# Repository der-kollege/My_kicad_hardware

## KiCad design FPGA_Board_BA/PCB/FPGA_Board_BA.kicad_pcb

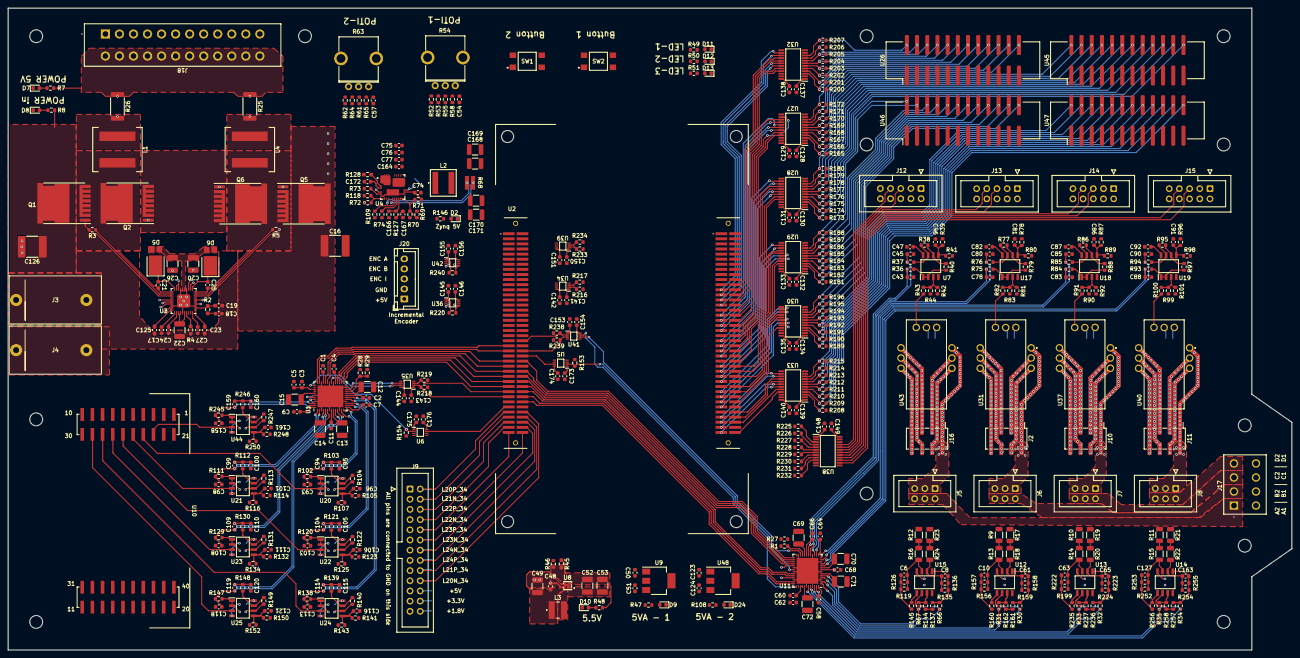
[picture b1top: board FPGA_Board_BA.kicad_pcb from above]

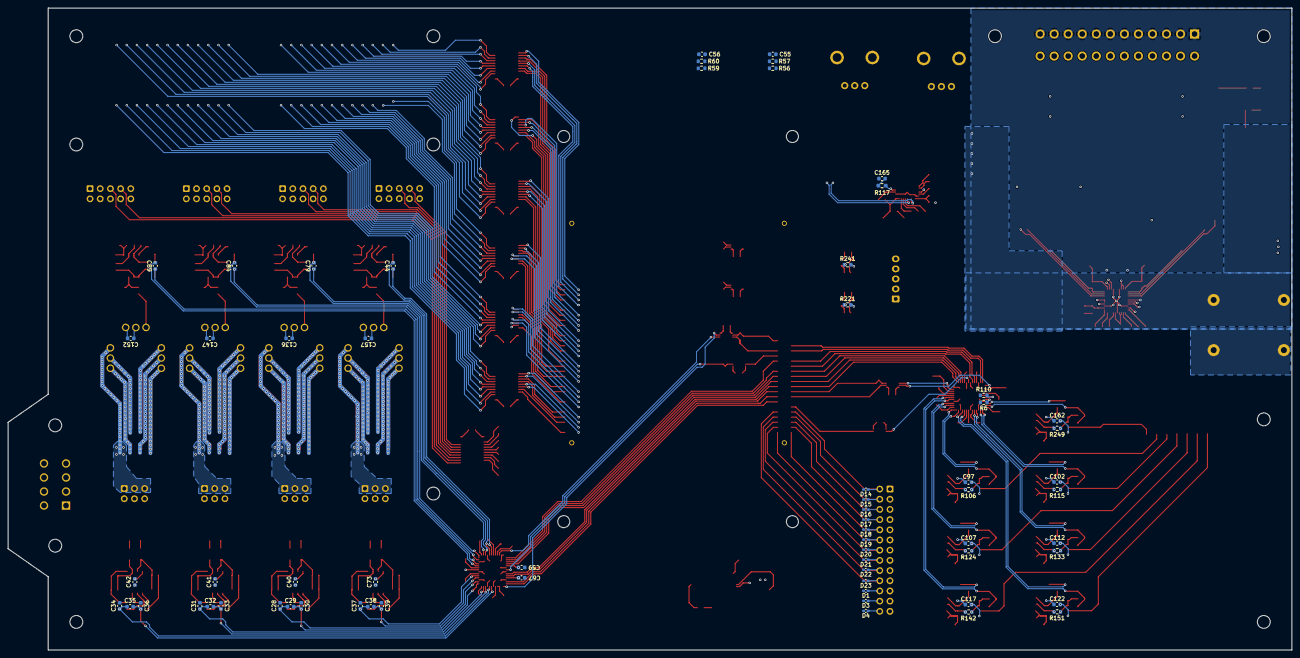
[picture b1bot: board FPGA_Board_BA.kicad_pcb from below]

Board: 4 copper layers, 320.0 x 160.0 mm, 524 parts (65 on the bottom side), 390 nets.

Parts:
C1, C2, C11, C24, C50, C51, C58, C59, C68, C123, C124: 1u_0603; C_0603
C3, C4, C5, C6, C7, C8, C9, C10, C40, C41, C42, C46, C47, C48, C54, C55, C56, C57, C60, C61, C62, C63, C64, C65, C66, C67, C73, C81, C82, C86, C87, C91, C92, C96, C97, C101, C102, C106, C107, C111, C112, C116, C117, C121, C122, C127, C128, C129, C130, C131, C132, C133, C134, C135, C136, C137, C138, C139, C140, C141, C142, C143, C144, C145, C146, C147, C148, C149, C150, C151, C152, C153, C154, C155, C156, C157, C161, C162, C163, C173, C174, C175, C176: 100n_0603; C_0603
C12, C13, C14, C15, C20, C22, C26, C49, C52, C53, C69, C70, C71, C72: 10u_1210; C_1210
C16, C126: 25uF_2220; C_2220_5650Metric_Pad1.97x5.40mm_HandSolder
C17, C21, C25, C27, C75, C76, C77, C164, C165: 4u7_0603; C_0603
C18: 1n_0603; C_0603
C19: 56pF_0603; C_0603_1608Metric_Pad1.08x0.95mm_HandSolder
C23, C125: 120nF_0603; C_0603_1608Metric_Pad1.08x0.95mm_HandSolder
C28, C29, C30, C31, C32, C33, C34, C35, C36, C37, C38, C39, C43, C44, C45, C78, C79, C80, C83, C84, C85, C88, C89, C90, C93, C94, C95, C98, C99, C100, C103, C104, C105, C108, C109, C110, C113, C114, C115, C118, C119, C120, C158, C159, C160: 15p_0603; C_0603
C74: 470n_0603; C_0603
C166: 220p_0603; R_0603_1608Metric
C167, C172: 15n_0603; C_0603
C168, C169, C170, C171: 47u_1210; C_1210_3225Metric
D1, D3, D4, D14, D15, D16, D17, D18, D19, D20, D21, D22, D23: B72590D50H160; C_0402_1005Metric_Pad0.74x0.62mm_HandSolder
D2, D7, D8, D9, D10, D12, D24: LED_G_0603; LED_0603_1608Metric
D5, D6: SBR10U200P5-13; SBR10U200P5
D11: LED_B_0603; LED_0603_1608Metric
D13: LED_R_0603; LED_0603_1608Metric
J2, J10, J11, J16: PinHeader_2x4_SMD; PinHeader_2x04_P2.54mm_Vertical_SMD
J3: Banana_Socket_Red; Banana_Socket_Altech_Red
J4: Banana_Socket_Black; Banana_Socket_Aletch_Black
J5, J6, J7, J8: Box_Header_6pin; IDC-Header_2x03_P2.54mm_Vertical
J9: Box_Header_26pin; IDC-Header_2x13_P2.54mm_Vertical
J12, J13, J14, J15: Box_Header_2x05_THT; IDC-Header_2x05_P2.54mm_Vertical
J17: Plug_Terminal_2x4_Vertical
J18: Plug_Terminal_2x12pin; DMCV 1,5_12-G1F-3,5-LR P20THR
J20: JST_XH_05_vertical; JST_XH_B5B-XH-A_1x05_P2.50mm_Vertical
L1, L4: XAL1010-152MED; L_Coilcraft_XAL1010-XXX
L2: Inductor 5.6uH; L_5u6_78439346056
L3: SMD_Inductor_1u; 74404043010A
Q1, Q2, Q5, Q6: IPT017N12NM6; Infineon_PG-HSOF-8-1
R1, R27, R28, R29, R72, R118, R220, R221, R240, R241: 0R_0603; R_0603_1608Metric
R2: 25k5_0603; R_0603_1608Metric_Pad0.98x0.95mm_HandSolder
R3, R5: 2R2_0603; R_0603_1608Metric
R4: 39k2_0603; R_0603_1608Metric_Pad0.98x0.95mm_HandSolder
R6, R43, R82, R91, R100, R110, R119, R126, R135, R136, R137, R144, R145, R156, R157, R158, R159, R160, R161, R162, R199, R222, R223, R224, R235, R236, R237, R252, R253, R254, R255, R256, R257, R258: 1k_0603; R_0603_1608Metric
R7, R47, R48, R49, R50, R51, R52, R53, R55, R57, R60, R61, R62, R64, R70, R108, R146, R153, R154, R165, R166, R167, R168, R169, R170, R171, R172, R173, R174, R175, R176, R177, R178, R179, R180, R181, R182, R183, R184, R185, R186, R187, R188, R189, R190, R191, R192, R193, R194, R195, R196, R200, R201, R202, R203, R204, R205, R206, R207, R208, R209, R210, R211, R212, R213, R214, R215, R216, R217, R218, R219, R225, R226, R227, R228, R229, R230, R231, R232, R233, R234, R238, R239: 10k_0603; R_0603_1608Metric
R8, R46, R73: 100k_0603; R_0603_1608Metric
R9, R10, R11, R12, R13, R14, R15, R16, R17, R18, R19, R20, R21, R22, R23, R24: 100k_1206; R_1206_3216Metric
R25, R26: 0R002_2512; R_2512_6332Metric
R30, R31, R32, R33, R34, R35, R36, R37, R66, R67, R75, R76, R84, R85, R93, R94, R102, R103, R111, R112, R120, R121, R129, R130, R138, R139, R147, R148, R245, R246: 30R_0603; R_0603_1608Metric
R38, R40, R77, R79, R86, R88, R95, R97, R104, R106, R113, R115, R122, R124, R131, R133, R140, R142, R149, R151, R247, R249: 500R_0603; R_0603_1608Metric
R39, R41, R78, R80, R87, R89, R96, R98, R105, R107, R114, R116, R123, R125, R132, R134, R141, R143, R150, R152, R248, R250: 5k1_0603; R_0603_1608Metric
R42, R44, R81, R83, R90, R92, R99, R101: 9k1_0603; R_0603_1608Metric
R45: 820k_0603; R_0603_1608Metric_Pad0.98x0.95mm_HandSolder
R54, R63: Poti_10k; RK09D1130A1N
R56, R58, R59, R65: 100R_0603; R_0603_1608Metric
R68: Shunt_0R006; PRL1632-R006-F-T1
R69: 52K3_0603; R_0603_1608Metric
R71: 24k9_0603; R_0603_1608Metric
R74: 71k5_0603; R_0603_1608Metric
R109: 41k2_0603; R_0603_1608Metric
R117, R128: 1R_0603; R_0603_1608Metric_Pad0.98x0.95mm_HandSolder
R127: 3k83_0603; R_0603_1608Metric
SW1, SW2: TL3305BF100QG; TL3305BF160QG
U1, U11: LTC2320-16_CMOS; UKG_52_7mm_8mm
U2: Zynq7020
U3: LM5143; VQFN 40 pin 5.8mm x 5.8mm
U4: LM70860RRXR; RRX Package, 29-Pin VQFN
U5, U6, U34, U35, U36, U39, U41, U42: SN74LXC2T45Q1; SN74LXC2T45QDCURQ1
U7, U12, U13, U14, U15, U17, U18, U19, U20, U21, U22, U23, U24, U25, U44: 1819_IS8; LT1819
U8: TPS61022
U9, U48: MCP1703AT-5002EDB; SOT-223
U10: BOOSTXL-3PHGANINV; TI_BOOSTXL_3PH
U26, U45, U46, U47: BoxHeader_24pin; IDC-Header_2x12_P2.54mm_Vertical_SMD
U27, U28, U29, U30, U32, U33, U38: SN74LXCH8T245RHLR; SN74LXCH8T245
U31, U37, U40, U43: S22P006S05; Tamura_S22P006S05

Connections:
+1V8: C1.1, C4.1, C59.1, C67.1, C144.1, C154.1, C173.2, C175.2, D4.1 (A1), J9.26, R1.2, R28.2, U1.31 (OVDD), U1.37 (OVDD), U2.b9 (XADC_VCC), U5.1 (VCCA), U6.1 (VCCA), U11.31 (OVDD), U11.37 (OVDD), U35.8 (VCCB), U41.8 (VCCB)
+3.3V: C129.1, C131.1, C133.1, C135.1, C138.1, C140.1, C142.1, C143.2, C146.1, C148.2, C151.1, C153.2, C156.1, C174.1, C176.1, D3.1 (A1), J9.24, R218.1, R219.1, R225.1, R226.1, R227.1, R228.1, R229.1, R230.1, R231.1, R232.1, R238.1, R239.1, SW1.3, SW1.4, SW2.3, SW2.4, U2.a3 (VDD_3V), U2.b3 (VDD_3V), U5.8 (VCCB), U6.8 (VCCB), U27.23 (V_{CCB}), U27.24 (V_{CCB}), U28.23 (V_{CCB}), U28.24 (V_{CCB}), U29.23 (V_{CCB}), U29.24 (V_{CCB}), U30.23 (V_{CCB}), U30.24 (V_{CCB}), U32.23 (V_{CCB}), U32.24 (V_{CCB}), U33.23 (V_{CCB}), U33.24 (V_{CCB}), U34.8 (VCCB), U35.1 (VCCA), U36.8 (VCCB), U38.1 (V_{CCA}), U38.2 (DIR), U39.8 (VCCB), U41.1 (VCCA), U42.8 (VCCB)
+5V: C48.1, C49.1, C128.2, C130.2, C132.2, C134.2, C137.2, C139.2, C141.2, C145.2, C149.1, C150.2, C155.2, D1.1 (A1), J9.22, J12.9, J12.10, J13.9, J13.10, J14.9, J14.10, J15.9, J15.10, J18.2, J18.4, J18.6, J18.8, J18.10, J18.12, J18.14, J18.16, J18.18, J18.20, J18.22, J18.24, J20.1, L3.1, R7.1, R25.1, R26.1, R165.1, R166.1, R167.1, R168.1, R169.1, R170.1, R171.1, R172.1, R173.1, R174.1, R175.1, R176.1, R177.1, R178.1, R179.1, R180.1, R181.1, R182.1, R183.1, R184.1, R185.1, R186.1, R187.1, R188.1, R189.1, R190.1, R191.1, R192.1, R193.1, R194.1, R195.1, R196.1, R200.1, R201.1, R202.1, R203.1, R204.1, R205.1, R206.1, R207.1, R208.1, R209.1, R210.1, R211.1, R212.1, R213.1, R214.1, R215.1, R216.1, R217.1, R220.1, R233.1, R234.1, R240.1, U3.5 (VOUT2), U3.6 (VCCX), U3.26 (VOUT1), U8.5 (EN), U8.7 (VIN), U27.1 (V_{CCA}), U27.2 (DIR), U28.1 (V_{CCA}), U28.2 (DIR), U29.1 (V_{CCA}), U29.2 (DIR), U30.1 (V_{CCA}), U30.2 (DIR), U32.1 (V_{CCA}), U32.2 (DIR), U33.1 (V_{CCA}), U33.2 (DIR), U34.1 (VCCA), U36.1 (VCCA), U38.23 (V_{CCB}), U38.24 (V_{CCB}), U39.1 (VCCA), U42.1 (VCCA)
+5VA: C2.1, C3.1, C5.1, C7.1, C9.1, C40.2, C41.2, C42.2, C47.1, C51.1, C58.1, C60.1, C62.1, C64.1, C66.1, C73.2, C82.1, C87.1, C92.1, C97.1, C102.1, C107.1, C112.1, C117.1, C122.1, C162.1, R47.1, R52.1, R53.1, R55.1, R61.1, R62.1, R64.1, U1.15 (VDD), U1.21 (VDD), U1.43 (REFBUFEN), U1.44 (VDD), U1.52 (VDD), U7.8 (V+), U9.3 (Vout), U11.15 (VDD), U11.21 (VDD), U11.43 (REFBUFEN), U11.44 (VDD), U11.52 (VDD), U12.4 (V-), U13.4 (V-), U14.4 (V-), U15.4 (V-), U17.8 (V+), U18.8 (V+), U19.8 (V+), U20.8 (V+), U21.8 (V+), U22.8 (V+), U23.8 (V+), U24.8 (V+), U25.8 (V+), U44.8 (V+)
+5VA_2: C124.1, C136.2, C147.2, C152.2, C157.2, R108.1, U31.9 (5V), U37.9 (5V), U40.9 (5V), U43.9 (5V), U48.3 (Vout)
+5V_Zynq: C168.2, C169.2, C170.2, C171.2, R68.2, R69.1, R146.1, U2.a1 (VDD_5V), U2.b1 (VDD_5V), U4.6 (BIAS), U4.12 (Vout)
/ADC for B6/CLK_IN: R218.2, U2.a65 (IO_L16N_T2_34), U35.2 (A1)
/ADC for B6/CLK_OUT: U2.a69 (IO_L18N_T2_34), U6.7 (B1)
/ADC for B6/Diffamp_1/Ain+: C158.1, C159.1, R245.1, U1.51 (Ain7+)
/ADC for B6/Diffamp_1/Ain-: C159.2, C160.1, R246.1, U1.50 (Ain7-)
/ADC for B6/Diffamp_2/Ain+: C93.1, C94.1, R102.1, U1.14 (Ain3+)
/ADC for B6/Diffamp_2/Ain-: C94.2, C95.1, R103.1, U1.13 (Ain3-)
/ADC for B6/Diffamp_3/Ain+: C98.1, C99.1, R111.1, U1.2 (Ain6+)
/ADC for B6/Diffamp_3/Ain-: C99.2, C100.1, R112.1, U1.1 (Ain6-)
/ADC for B6/Diffamp_4/Ain+: C103.1, C104.1, R120.1, U1.17 (Ain2+)
/ADC for B6/Diffamp_4/Ain-: C104.2, C105.1, R121.1, U1.16 (Ain2-)
/ADC for B6/Diffamp_5/Ain+: C108.1, C109.1, R129.1, U1.5 (Ain5+)
/ADC for B6/Diffamp_5/Ain-: C109.2, C110.1, R130.1, U1.4 (Ain5-)
/ADC for B6/Diffamp_6/Ain+: C113.1, C114.1, R138.1, U1.20 (Ain1+)
/ADC for B6/Diffamp_6/Ain-: C114.2, C115.1, R139.1, U1.19 (Ain1-)
/ADC for B6/Diffamp_7/Ain+: C118.1, C119.1, R147.1, U1.11 (Ain4+)
/ADC for B6/Diffamp_7/Ain-: C119.2, C120.1, R148.1, U1.10 (Ain4-)
/ADC for B6/I_A: U10.27 (IA), U23.3 (+)
/ADC for B6/I_B: U10.28 (IB), U24.3 (+)
/ADC for B6/I_C: U10.29 (IC), U25.3 (+)
/ADC for B6/LS CLKOUT/A1: R154.1, U1.33 (CLKOUT+), U6.2 (A1)
/ADC for B6/Level Shift for DIO/B1: U1.41 (SCK), U35.7 (B1)
/ADC for B6/Level Shift for DIO/B2: U1.24 (~CNV), U35.6 (B2)
/ADC for B6/SDO1: U1.27 (SDO1), U2.a59 (IO_L14P_T2_34)
/ADC for B6/SDO2: U1.28 (SDO2), U2.a61 (IO_L14N_T2_34)
/ADC for B6/SDO3: U1.29 (SDO3), U2.a57 (IO_L12N_T1_34)
/ADC for B6/SDO4: U1.30 (SDO4), U2.a55 (IO_L12P_T1_34)
/ADC for B6/SDO5: U1.35 (SDO5), U2.a53 (IO_L9N_T2_34)
/ADC for B6/SDO6: U1.36 (SDO6), U2.a51 (IO_L9P_T1_34)
/ADC for B6/SDO7: U1.39 (SDO7), U2.a47 (IO_L11N_T1_34)
/ADC for B6/SDO8: U1.40 (SDO8), U2.a43 (IO_L8N_T1_34)
/ADC for B6/V_A: U10.24 (VA), U20.3 (+)
/ADC for B6/V_B: U10.25 (VB), U21.3 (+)
/ADC for B6/V_C: U10.26 (VC), U22.3 (+)
/ADC for B6/V_DC: U10.23 (VDC), U44.3 (+)
/ADC for B6/~CNV: R219.2, U2.a63 (IO_L16P_T2_34), U35.3 (A2)
/ADC for Machine/CLK_IN_1: R238.2, U2.a46 (IO_L10P_T1_34), U41.2 (A1)
/ADC for Machine/CLK_OUT_1: U2.a50 (IO_L13P_T2_34), U5.7 (B1)
/ADC for Machine/Diffamp5/Ain+: C43.1, C44.1, R36.1, U11.20 (Ain1+)
/ADC for Machine/Diffamp5/Ain-: C44.2, C45.1, R37.1, U11.19 (Ain1-)
/ADC for Machine/Diffamp6/Ain+: C78.1, C79.1, R75.1, U11.17 (Ain2+)
/ADC for Machine/Diffamp6/Ain-: C79.2, C80.1, R76.1, U11.16 (Ain2-)
/ADC for Machine/Diffamp7/Ain+: C83.1, C84.1, R84.1, U11.14 (Ain3+)
/ADC for Machine/Diffamp7/Ain-: C84.2, C85.1, R85.1, U11.13 (Ain3-)
/ADC for Machine/Diffamp8/Ain+: C88.1, C89.1, R93.1, U11.11 (Ain4+)
/ADC for Machine/Diffamp8/Ain-: C89.2, C90.1, R94.1, U11.10 (Ain4-)
/ADC for Machine/LS CLKOUT/A1: R153.1, U5.2 (A1), U11.33 (CLKOUT+)
/ADC for Machine/Level Shift for DIO/B1: U11.41 (SCK), U41.7 (B1)
/ADC for Machine/Level Shift for DIO/B2: U11.24 (~CNV), U41.6 (B2)
/ADC for Machine/SDO1_1: U2.a52 (IO_L13N_T2_34), U11.27 (SDO1)
/ADC for Machine/SDO2_1: U2.a56 (IO_L15P_T2_34), U11.28 (SDO2)
/ADC for Machine/SDO3_1: U2.a58 (IO_L15N_T2_34), U11.29 (SDO3)
/ADC for Machine/SDO4_1: U2.a60 (IO_L17P_T2_34), U11.30 (SDO4)
/ADC for Machine/SDO5_1: U2.a62 (IO_L17N_T2_34), U11.35 (SDO5)
/ADC for Machine/SDO6_1: U2.a64 (IO_L19P_T3_34), U11.36 (SDO6)
/ADC for Machine/SDO7_1: U2.a66 (IO_L19N_T3_34), U11.39 (SDO7)
/ADC for Machine/SDO8_1: U2.a70 (IO_L18P_T2_34), U11.40 (SDO8)
/ADC for Machine/~CNV_1: R239.2, U2.a48 (IO_L10N_T1_34), U41.3 (A2)
/Analog Voltage/5.5V: C50.1, C52.1, C53.1, C123.1, R45.1, R48.1, U8.3 (VOUT), U9.1 (Vin), U48.1 (Vin)
/CHB Communication/En_Ph1: R225.2, U38.3 (A1)
/CHB Communication/En_Ph2: R227.2, U38.5 (A3)
/CHB Communication/En_Ph3: R229.2, U38.7 (A5)
/CHB Communication/En_Ph4: R231.2, U38.9 (A7)
/CHB Communication/Level_Shifter_8bit_1/A1: R200.2, U26.16, U32.3 (A1)
/CHB Communication/Level_Shifter_8bit_1/A2: R201.2, U26.14, U32.4 (A2)
/CHB Communication/Level_Shifter_8bit_1/A3: R202.2, U26.12, U32.5 (A3)
/CHB Communication/Level_Shifter_8bit_1/A4: R203.2, U26.10, U32.6 (A4)
/CHB Communication/Level_Shifter_8bit_1/A5: R204.2, U26.8, U32.7 (A5)
/CHB Communication/Level_Shifter_8bit_1/A6: R205.2, U26.6, U32.8 (A6)
/CHB Communication/Level_Shifter_8bit_1/A7: R206.2, U26.4, U32.9 (A7)
/CHB Communication/Level_Shifter_8bit_2/A1: R165.2, U27.3 (A1), U45.8
/CHB Communication/Level_Shifter_8bit_2/A2: R166.2, U27.4 (A2), U45.6
/CHB Communication/Level_Shifter_8bit_2/A3: R167.2, U27.5 (A3), U45.4
/CHB Communication/Level_Shifter_8bit_2/A5: R169.2, U26.24, U27.7 (A5)
/CHB Communication/Level_Shifter_8bit_2/A6: R170.2, U26.22, U27.8 (A6)
/CHB Communication/Level_Shifter_8bit_2/A7: R171.2, U26.20, U27.9 (A7)
/CHB Communication/Level_Shifter_8bit_2/A8: R172.2, U26.18, U27.10 (A8)
/CHB Communication/Level_Shifter_8bit_3/A1: R173.2, U28.3 (A1), U45.24
/CHB Communication/Level_Shifter_8bit_3/A2: R174.2, U28.4 (A2), U45.22
/CHB Communication/Level_Shifter_8bit_3/A3: R175.2, U28.5 (A3), U45.20
/CHB Communication/Level_Shifter_8bit_3/A4: R176.2, U28.6 (A4), U45.18
/CHB Communication/Level_Shifter_8bit_3/A5: R177.2, U28.7 (A5), U45.16
/CHB Communication/Level_Shifter_8bit_3/A6: R178.2, U28.8 (A6), U45.14
/CHB Communication/Level_Shifter_8bit_3/A7: R179.2, U28.9 (A7), U45.12
/CHB Communication/Level_Shifter_8bit_3/A8: R180.2, U28.10 (A8), U45.10
/CHB Communication/Level_Shifter_8bit_4/A1: R181.2, U29.3 (A1), U46.16
/CHB Communication/Level_Shifter_8bit_4/A2: R182.2, U29.4 (A2), U46.14
/CHB Communication/Level_Shifter_8bit_4/A3: R183.2, U29.5 (A3), U46.12
/CHB Communication/Level_Shifter_8bit_4/A4: R184.2, U29.6 (A4), U46.10
/CHB Communication/Level_Shifter_8bit_4/A5: R185.2, U29.7 (A5), U46.8
/CHB Communication/Level_Shifter_8bit_4/A6: R186.2, U29.8 (A6), U46.6
/CHB Communication/Level_Shifter_8bit_4/A7: R187.2, U29.9 (A7), U46.4
/CHB Communication/Level_Shifter_8bit_5/A1: R189.2, U30.3 (A1), U47.8
/CHB Communication/Level_Shifter_8bit_5/A2: R190.2, U30.4 (A2), U47.6
/CHB Communication/Level_Shifter_8bit_5/A3: R191.2, U30.5 (A3), U47.4
/CHB Communication/Level_Shifter_8bit_5/A5: R193.2, U30.7 (A5), U46.24
/CHB Communication/Level_Shifter_8bit_5/A6: R194.2, U30.8 (A6), U46.22
/CHB Communication/Level_Shifter_8bit_5/A7: R195.2, U30.9 (A7), U46.20
/CHB Communication/Level_Shifter_8bit_5/A8: R196.2, U30.10 (A8), U46.18
/CHB Communication/Level_Shifter_8bit_6/A1: R208.2, U33.3 (A1), U47.24
/CHB Communication/Level_Shifter_8bit_6/A2: R209.2, U33.4 (A2), U47.22
/CHB Communication/Level_Shifter_8bit_6/A3: R210.2, U33.5 (A3), U47.20
/CHB Communication/Level_Shifter_8bit_6/A4: R211.2, U33.6 (A4), U47.18
/CHB Communication/Level_Shifter_8bit_6/A5: R212.2, U33.7 (A5), U47.16
/CHB Communication/Level_Shifter_8bit_6/A6: R213.2, U33.8 (A6), U47.14
/CHB Communication/Level_Shifter_8bit_6/A7: R214.2, U33.9 (A7), U47.12
/CHB Communication/Level_Shifter_8bit_6/A8: R215.2, U33.10 (A8), U47.10
/CHB Communication/Level_shifter_Rx_En/B1: J12.7, U38.21 (B1)
/CHB Communication/Level_shifter_Rx_En/B2: J12.5, U38.20 (B2)
/CHB Communication/Level_shifter_Rx_En/B3: J13.7, U38.19 (B3)
/CHB Communication/Level_shifter_Rx_En/B4: J13.5, U38.18 (B4)
/CHB Communication/Level_shifter_Rx_En/B5: J14.7, U38.17 (B5)
/CHB Communication/Level_shifter_Rx_En/B6: J14.5, U38.16 (B6)
/CHB Communication/Level_shifter_Rx_En/B7: J15.7, U38.15 (B7)
/CHB Communication/Level_shifter_Rx_En/B8: J15.5, U38.14 (B8)
/CHB Communication/Level_shifter_error_1/A1: J12.1, R233.2, U39.2 (A1)
/CHB Communication/Level_shifter_error_1/A2: J13.1, R234.2, U39.3 (A2)
/CHB Communication/Level_shifter_error_2/A1: J14.1, R216.2, U34.2 (A1)
/CHB Communication/Level_shifter_error_2/A2: J15.1, R217.2, U34.3 (A2)
/CHB Communication/Ph_A_Tx1: U2.b23 (IO_L1P_T0_35), U32.14 (B8)
/CHB Communication/Ph_A_Tx1_5V: J12.3, R207.2, U26.2, U32.10 (A8)
/CHB Communication/Ph_A_Tx2: U2.b25 (IO_L1N_T0_35), U32.15 (B7)
/CHB Communication/Ph_A_Tx3: U2.b22 (IO_L2P_T0_35), U32.16 (B6)
/CHB Communication/Ph_A_Tx4: U2.b24 (IO_L2N_T0_35), U32.17 (B5)
/CHB Communication/Ph_A_Tx5: U2.b27 (IO_L3P_T0_35), U32.18 (B4)
/CHB Communication/Ph_A_Tx6: U2.b29 (IO_L3N_T0_35), U32.19 (B3)
/CHB Communication/Ph_A_Tx7: U2.b26 (IO_L4P_T0_35), U32.20 (B2)
/CHB Communication/Ph_A_Tx8: U2.b28 (IO_L4N_T0_35), U32.21 (B1)
/CHB Communication/Ph_A_Tx9: U2.b34 (IO_L6N_T0_35), U27.14 (B8)
/CHB Communication/Ph_A_Tx10: U2.b32 (IO_L6P_T0_35), U27.15 (B7)
/CHB Communication/Ph_A_Tx11: U2.b35 (IO_L5N_T0_35), U27.16 (B6)
/CHB Communication/Ph_A_Tx12: U2.b33 (IO_L5P_T0_35), U27.17 (B5)
/CHB Communication/Ph_B_Tx1: U2.b37 (IO_L7P_T1_35), U27.18 (B4)
/CHB Communication/Ph_B_Tx1_5V: J13.3, R168.2, U27.6 (A4), U45.2
/CHB Communication/Ph_B_Tx2: U2.b39 (IO_L7N_T1_35), U27.19 (B3)
/CHB Communication/Ph_B_Tx3: U2.b36 (IO_L8P_T1_35), U27.20 (B2)
/CHB Communication/Ph_B_Tx4: U2.b38 (IO_L8N_T1_35), U27.21 (B1)
/CHB Communication/Ph_B_Tx5: U2.b43 (IO_L9P_T1_35), U28.14 (B8)
/CHB Communication/Ph_B_Tx6: U2.b45 (IO_L9N_T1_35), U28.15 (B7)
/CHB Communication/Ph_B_Tx7: U2.b42 (IO_L10P_T1_35), U28.16 (B6)
/CHB Communication/Ph_B_Tx8: U2.b44 (IO_L10N_T1_35), U28.17 (B5)
/CHB Communication/Ph_B_Tx9: U2.b47 (IO_L11P_T1_35), U28.18 (B4)
/CHB Communication/Ph_B_Tx10: U2.b49 (IO_L11N_T1_35), U28.19 (B3)
/CHB Communication/Ph_B_Tx11: U2.b46 (IO_L12P_T1_35), U28.20 (B2)
/CHB Communication/Ph_B_Tx12: U2.b48 (IO_L12N_T1_35), U28.21 (B1)
/CHB Communication/Ph_C_Tx1: U2.b53 (IO_L13P_35), U29.14 (B8)
/CHB Communication/Ph_C_Tx1_5V: J14.3, R188.2, U29.10 (A8), U46.2
/CHB Communication/Ph_C_Tx2: U2.b55 (IO_L13N_35), U29.15 (B7)
/CHB Communication/Ph_C_Tx3: U2.b52 (IO_L14P_T2_35), U29.16 (B6)
/CHB Communication/Ph_C_Tx4: U2.b54 (IO_L14N_T2_35), U29.17 (B5)
/CHB Communication/Ph_C_Tx5: U2.b57 (IO_L15P_T2_35), U29.18 (B4)
/CHB Communication/Ph_C_Tx6: U2.b59 (IO_L15N_T2_35), U29.19 (B3)
/CHB Communication/Ph_C_Tx7: U2.b56 (IO_L16P_T2_35), U29.20 (B2)
/CHB Communication/Ph_C_Tx8: U2.b58 (IO_L16N_T2_35), U29.21 (B1)
/CHB Communication/Ph_C_Tx9: U2.b63 (IO_L17P_T2_35), U30.14 (B8)
/CHB Communication/Ph_C_Tx10: U2.b65 (IO_L17N_T2_35), U30.15 (B7)
/CHB Communication/Ph_C_Tx11: U2.b62 (IO_L18P_T2_35), U30.16 (B6)
/CHB Communication/Ph_C_Tx12: U2.b64 (IO_L18N_T2_35), U30.17 (B5)
/CHB Communication/Ph_D_Tx1: U2.b67 (IO_L19P_T3_35), U30.18 (B4)
/CHB Communication/Ph_D_Tx1_5V: J15.3, R192.2, U30.6 (A4), U47.2
/CHB Communication/Ph_D_Tx2: U2.b69 (IO_L19N_T3_35), U30.19 (B3)
/CHB Communication/Ph_D_Tx3: U2.b66 (IO_L20P_T3_35), U30.20 (B2)
/CHB Communication/Ph_D_Tx4: U2.b68 (IO_L20N_T3_35), U30.21 (B1)
/CHB Communication/Ph_D_Tx5: U2.b73 (IO_L21P_T3_35), U33.14 (B8)
/CHB Communication/Ph_D_Tx6: U2.b75 (IO_L21N_T3_35), U33.15 (B7)
/CHB Communication/Ph_D_Tx7: U2.b72 (IO_L22P_T3_35), U33.16 (B6)
/CHB Communication/Ph_D_Tx8: U2.b74 (IO_L22N_T3_35), U33.17 (B5)
/CHB Communication/Ph_D_Tx9: U2.b77 (IO_L23P_T3_35), U33.18 (B4)
/CHB Communication/Ph_D_Tx10: U2.b79 (IO_L23N_T3_35), U33.19 (B3)
/CHB Communication/Ph_D_Tx11: U2.b76 (IO_L24P_T3_35), U33.20 (B2)
/CHB Communication/Ph_D_Tx12: U2.b78 (IO_L24N_T3_35), U33.21 (B1)
/CHB Communication/Rx_Ph1: R226.2, U38.4 (A2)
/CHB Communication/Rx_Ph2: R228.2, U38.6 (A4)
/CHB Communication/Rx_Ph3: R230.2, U38.8 (A6)
/CHB Communication/Rx_Ph4: R232.2, U38.10 (A8)
/CHB to 3Ph/Ph_A2_out: J5.2, J5.4, J5.6, J17.1, R23.1
/CHB to 3Ph/Ph_B2_out: J6.2, J6.4, J6.6, J17.2 (Pin_3), R17.1
/CHB to 3Ph/Ph_C2_out: J7.2, J7.4, J7.6, J17.3 (Pin_5), R19.1
/CHB to 3Ph/Ph_D2_out: J8.2, J8.4, J8.6, J17.4 (Pin_7), R21.1
/Current measure/Tamura_1/pin1: J5.1, J5.3, J5.5, J16.1, J16.2, U43.1 (In_1)
/Current measure/Tamura_1/pin2: J16.3, U43.2 (In_2)
/Current measure/Tamura_1/pin3: J16.4, U43.3 (In_3)
/Current measure/Tamura_1/pin4: J16.7, J16.8, J17.5 (Pin_2), R12.1, U43.4 (Out_1)
/Current measure/Tamura_1/pin5: J16.6, U43.5 (Out_2)
/Current measure/Tamura_1/pin6: J16.5, U43.6 (Out_3)
/Current measure/Tamura_2/pin1: J2.1, J2.2, J6.1, J6.3, J6.5, U31.1 (In_1)
/Current measure/Tamura_2/pin2: J2.3, U31.2 (In_2)
/Current measure/Tamura_2/pin3: J2.4, U31.3 (In_3)
/Current measure/Tamura_2/pin4: J2.7, J2.8, J17.6 (Pin_4), R9.1, U31.4 (Out_1)
/Current measure/Tamura_2/pin5: J2.6, U31.5 (Out_2)
/Current measure/Tamura_2/pin6: J2.5, U31.6 (Out_3)
/Current measure/Tamura_3/pin1: J7.1, J7.3, J7.5, J10.1, J10.2, U37.1 (In_1)
/Current measure/Tamura_3/pin2: J10.3, U37.2 (In_2)
/Current measure/Tamura_3/pin3: J10.4, U37.3 (In_3)
/Current measure/Tamura_3/pin4: J10.7, J10.8, J17.7 (Pin_6), R10.1, U37.4 (Out_1)
/Current measure/Tamura_3/pin5: J10.6, U37.5 (Out_2)
/Current measure/Tamura_3/pin6: J10.5, U37.6 (Out_3)
/Current measure/Tamura_4/pin1: J8.1, J8.3, J8.5, J11.1, J11.2, U40.1 (In_1)
/Current measure/Tamura_4/pin2: J11.3, U40.2 (In_2)
/Current measure/Tamura_4/pin3: J11.4, U40.3 (In_3)
/Current measure/Tamura_4/pin4: J11.7, J11.8, J17.8, R11.1, U40.4 (Out_1)
/Current measure/Tamura_4/pin5: J11.6, U40.5 (Out_2)
/Current measure/Tamura_4/pin6: J11.5, U40.6 (Out_3)
/Encoder/ENC_A_5V: J20.5, U42.2 (A1)
/Encoder/ENC_B_5V: J20.4, U42.3 (A2)
/Encoder/ENC_I_5V: J20.3, U36.2 (A1)
/FPGA/B6_En: U2.a16 (IO_L14P_T2_13), U10.13 (En)
/FPGA/Button1: C55.1, R56.2, R57.1
/FPGA/Button2: C56.1, R59.2, R60.1
/FPGA/Freepin1: D23.1 (A1), J9.20, U2.a72 (IO_L20N_T3_34)
/FPGA/Freepin2: D22.1 (A1), J9.18, U2.a74 (IO_L21P_T3_34)
/FPGA/Freepin3: D21.1 (A1), J9.16, U2.a76 (IO_L24P_T3_34)
/FPGA/Freepin4: D20.1 (A1), J9.14, U2.a78 (IO_L24N_T3_34)
/FPGA/Freepin5: D19.1 (A1), J9.12, U2.a80 (IO_L23N_T3_34)
/FPGA/Freepin6: D18.1 (A1), J9.10, U2.a79 (IO_L23P_T3_34)
/FPGA/Freepin7: D17.1 (A1), J9.8, U2.a77 (IO_L22N_T3_34)
/FPGA/Freepin8: D16.1 (A1), J9.6, U2.a75 (IO_L22P_T3_34)
/FPGA/Freepin9: D15.1 (A1), J9.4, U2.a73 (IO_L21N_T3_34)
/FPGA/Freepin10: D14.1 (A1), J9.2, U2.a71 (IO_L20P_T3_34)
/FPGA/OT: U2.a18 (IO_L14N_T2_13), U10.34 (OT)
/FPGA/PWM_AH: U2.a7 (IO_L11P_T1_13), U10.40 (PWM_AH)
/FPGA/PWM_AL: U2.a9 (IO_L11N_T1_13), U10.39 (PWM_AL)
/FPGA/PWM_BH: U2.a11 (IO_L12P_T1_13), U10.38 (PWM_BH)
/FPGA/PWM_BL: U2.a13 (IO_L12N_T1_13), U10.37 (PWM_BL)
/FPGA/PWM_CH: U2.a17 (IO_L13P_T2_13), U10.36 (PWM_CH)
/FPGA/PWM_CL: U2.a19 (IO_L13N_T2_13), U10.35 (PWM_CL)
/FPGA/Poti: R58.2, U2.b5 (XADC_INP0)
/FPGA/Poti2: R65.2, U2.b6 (DXP_0)
/Main_DCDC/Comp1: C19.1, R2.2, U3.2 (COMP2), U3.29 (COMP1)
/Main_DCDC/Leg-1/Gate_H: Q1.1 (G), R3.1, U3.23 (HOL1)
/Main_DCDC/Leg-1/Gate_L: Q2.1 (G), U3.18 (LO1), U3.19 (LOL1)
/Main_DCDC/Leg-1/R_I+: L1.1, R26.2, U3.27 (CS1)
/Main_DCDC/Leg-1/SW: C21.2, L1.2, Q1.2 (S), Q2.3 (D), U3.21 (SW1)
/Main_DCDC/Leg-2/Gate_H: Q5.1 (G), R5.1, U3.8 (HOL2)
/Main_DCDC/Leg-2/Gate_L: Q6.1 (G), U3.12 (LOL2), U3.13 (LO2)
/Main_DCDC/Leg-2/R_I+: L4.1, R25.2, U3.4 (CS2)
/Main_DCDC/Leg-2/SW: C25.2, L4.2, Q5.2 (S), Q6.3 (D), U3.10 (SW2)
/Main_DCDC/Mode: C22.1, U3.33 (DEMB), U3.34 (MODE), U3.36 (VDDA)
/Main_DCDC/Vin: C16.1, C17.1, C27.1, C75.1, C76.1, C77.1, C126.1, C164.1, J3.1, Q1.3 (D), Q5.3 (D), R8.1, R72.1, U3.25 (VIN), U3.31 (EN1), U3.40 (EN2), U4.1 (Vin), U4.2 (Vin), U4.3 (Vin), U4.27 (Vin), U4.28 (Vin), U4.29 (Vin)
/Voltage Measure/PHA_V+: C37.1, C38.1, R66.1
/Voltage Measure/PHA_V-: C38.2, C39.1, R67.1
/Voltage Measure/PHB_V+: C28.1, C29.1, R30.1
/Voltage Measure/PHB_V-: C29.2, C30.1, R31.1
/Voltage Measure/PHC_V+: C31.1, C32.1, R32.1
/Voltage Measure/PHC_V-: C32.2, C33.1, R33.1
/Voltage Measure/PHD_V+: C34.1, C35.1, R34.1
/Voltage Measure/PHD_V-: C35.2, C36.1, R35.1
/Zynq_5V/CBOOT: R128.2, U4.4 (CBOOT)
/Zynq_5V/FB: R69.2, R70.1, R71.1, U4.16 (FB)
/Zynq_5V/SW: C172.2, L2.1, U4.5 (SW), U4.20 (SW), U4.21 (SW), U4.22 (SW)
GND: C1.2, C2.2, C3.2, C4.2, C5.2, C7.2, C9.2, C11.2, C12.2, C13.2, C14.2, C15.2, C16.2, C17.2, C18.2, C19.2, C20.2, C22.2, C23.2, C24.2, C26.2, C27.2, C28.2, C30.2, C31.2, C33.2, C34.2, C36.2, C37.2, C39.2, C40.1, C41.1, C42.1, C43.2, C45.2, C46.2, C47.2, C48.2, C49.2, C50.2, C51.2, C52.2, C53.2, C54.2, C55.2, C56.2, C57.2, C58.2, C59.2, C60.2, C62.2, C64.2, C66.2, C67.2, C68.2, C69.2, C70.2, C71.2, C72.2, C73.1, C74.2, C75.2, C76.2, C77.2, C78.2, C80.2, C81.2, C82.2, C83.2, C85.2, C86.2, C87.2, C88.2, C90.2, C91.2, C92.2, C93.2, C95.2, C96.2, C97.2, C98.2, C100.2, C101.2, C102.2, C103.2, C105.2, C106.2, C107.2, C108.2, C110.2, C111.2, C112.2, C113.2, C115.2, C116.2, C117.2, C118.2, C120.2, C121.2, C122.2, C123.2, C124.2, C125.2, C126.2, C128.1, C129.2, C130.1, C131.2, C132.1, C133.2, C134.1, C135.2, C136.1, C137.1, C138.2, C139.1, C140.2, C141.1, C142.2, C143.1, C144.2, C145.1, C146.2, C147.1, C148.1, C149.2, C150.1, C151.2, C152.1, C153.1, C154.2, C155.1, C156.2, C157.1, C158.2, C160.2, C161.2, C162.2, C164.2, C165.2, C166.1, C167.2, C168.1, C169.1, C170.1, C171.1, C173.1, C174.2, C175.1, C176.2, D1.2 (A2), D2.1 (K), D3.2 (A2), D4.2 (A2), D7.1 (K), D8.1 (K), D9.1 (K), D10.1 (K), D11.1 (K), D12.1 (K), D13.1 (K), D14.2 (A2), D15.2 (A2), D16.2 (A2), D17.2 (A2), D18.2 (A2), D19.2 (A2), D20.2 (A2), D21.2 (A2), D22.2 (A2), D23.2 (A2), D24.1 (K), J4.1, J9.1, J9.3, J9.5, J9.7, J9.9, J9.11, J9.13, J9.15, J9.17, J9.19, J9.21, J9.23, J9.25, J12.2, J12.4, J12.6, J12.8, J13.2, J13.4, J13.6, J13.8, J14.2, J14.4, J14.6, J14.8, J15.2, J15.4, J15.6, J15.8, J18.1, J18.3, J18.5, J18.7, J18.9, J18.11, J18.13, J18.15, J18.17, J18.19, J18.21, J18.23, J20.2, Q2.2 (S), Q6.2 (S), R4.1, R6.2, R27.2, R29.2, R39.1, R42.2, R44.2, R46.2, R54.3, R54.4, R54.5, R57.2, R60.2, R63.3, R63.4, R63.5, R70.2, R73.1, R74.1, R78.1, R81.2, R83.2, R87.1, R90.2, R92.2, R96.1, R99.2, R101.2, R105.1, R109.1, R110.2, R114.1, R118.1, R123.1, R132.1, R141.1, R150.1, R153.2, R154.2, R221.1, R241.1, R248.1, U1.3 (GND), U1.7 (GND), U1.12 (GND), U1.18 (GND), U1.25 (~CMOS/LVDS), U1.26 (GND), U1.32 (GND), U1.34 (CLKOUT-), U1.38 (GND), U1.46 (GND), U1.49 (GND), U1.53 (GND), U2.a2 (GND), U2.a4 (GND), U2.a24 (GND), U2.a25 (GND), U2.a34 (GND), U2.a35 (GND), U2.a44 (GND), U2.a54 (GND), U2.a67 (GND), U2.a68 (GND), U2.b2 (GND), U2.b4 (GND), U2.b7 (XADC_INN0), U2.b8 (DXN_0), U2.b10 (GND), U2.b20 (GND), U2.b21 (GND), U2.b30 (GND), U2.b31 (GND), U2.b40 (GND), U2.b41 (GND), U2.b50 (GND), U2.b60 (GND), U2.b61 (GND), U2.b70 (GND), U2.b71 (GND), U2.b80 (GND), U3.3 (FB2), U3.14 (PGND2), U3.17 (PGND1), U3.28 (FB1), U3.35 (AGND), U3.41 (Pad), U4.8 (PFM/SYNCIN), U4.17 (AGND), U4.23 (PGND), U4.24 (PGND), U4.25 (PGND), U4.26 (PGND), U4.30 (PGND), U5.4 (GND), U5.5 (DIR), U6.4 (GND), U6.5 (DIR), U7.4 (V-), U8.1 (GND), U8.6 (MODE), U9.2 (GND), U9.4 (GND), U10.20 (GND), U10.22 (GND), U11.3 (GND), U11.7 (GND), U11.12 (GND), U11.18 (GND), U11.25 (~CMOS/LVDS), U11.26 (GND), U11.32 (GND), U11.34 (CLKOUT-), U11.38 (GND), U11.46 (GND), U11.49 (GND), U11.53 (GND), U12.8 (V+), U13.8 (V+), U14.8 (V+), U15.8 (V+), U17.4 (V-), U18.4 (V-), U19.4 (V-), U20.4 (V-), U21.4 (V-), U22.4 (V-), U23.4 (V-), U24.4 (V-), U25.4 (V-), U26.1, U26.3, U26.5, U26.7, U26.9, U26.11, U26.13, U26.15, U26.17, U26.19, U26.21, U26.23, U27.11 (GND), U27.12 (GND), U27.13 (GND), U27.22 (~OE), U28.11 (GND), U28.12 (GND), U28.13 (GND), U28.22 (~OE), U29.11 (GND), U29.12 (GND), U29.13 (GND), U29.22 (~OE), U30.11 (GND), U30.12 (GND), U30.13 (GND), U30.22 (~OE), U31.8 (GND), U32.11 (GND), U32.12 (GND), U32.13 (GND), U32.22 (~OE), U33.11 (GND), U33.12 (GND), U33.13 (GND), U33.22 (~OE), U34.4 (GND), U34.5 (DIR), U35.4 (GND), U35.5 (DIR), U36.4 (GND), U37.8 (GND), U38.11 (GND), U38.12 (GND), U38.13 (GND), U38.22 (~OE), U39.4 (GND), U39.5 (DIR), U40.8 (GND), U41.4 (GND), U41.5 (DIR), U42.4 (GND), U43.8 (GND), U44.4 (V-), U45.1, U45.3, U45.5, U45.7, U45.9, U45.11, U45.13, U45.15, U45.17, U45.19, U45.21, U45.23, U46.1, U46.3, U46.5, U46.7, U46.9, U46.11, U46.13, U46.15, U46.17, U46.19, U46.21, U46.23, U47.1, U47.3, U47.5, U47.7, U47.9, U47.11, U47.13, U47.15, U47.17, U47.19, U47.21, U47.23, U48.2 (GND), U48.4 (GND)
unnamed: C8.2, R66.2, R135.2, R136.2, R137.1, U15.1
unnamed: C18.1, R2.1
unnamed: C54.1, R54.2, R58.1
unnamed: C57.1, R63.2, R65.1
unnamed: C61.2, R30.2, R158.2, R159.2, R161.1, U12.1
unnamed: C65.2, R32.2, R223.2, R224.2, R236.1, U13.1
unnamed: C163.2, R34.2, R254.2, R255.2, R257.1, U14.1
unnamed: C165.1, R117.2
unnamed: C167.1, R127.1
unnamed: C172.1, R128.1
unnamed: D2.2 (A), R146.2
unnamed: C20.1, C26.1, D5.2 (A), D6.2 (A), U3.15 (VCC), U3.16 (VCC)
unnamed: C21.1, D5.1 (K), U3.20 (HB1)
unnamed: C25.1, D6.1 (K), U3.11 (HB2)
unnamed: D7.2 (A), R7.2
unnamed: D8.2 (A), R8.2
unnamed: D9.2 (A), R47.2
unnamed: D10.2 (A), R48.2
unnamed: D11.2 (A), R49.2
unnamed: D12.2 (A), R50.2
unnamed: D13.2 (A), R51.2
unnamed: D24.2 (A), R108.2
unnamed: R10.2, R14.1
unnamed: R11.2, R15.1
unnamed: R12.2, R16.1
unnamed: R9.2, R13.1
unnamed: R17.2, R18.1
unnamed: R19.2, R20.1
unnamed: R21.2, R22.1
unnamed: R23.2, R24.1
unnamed: R37.2, R38.1, U7.7
unnamed: R52.2, R53.2, R54.1, R55.2
unnamed: R56.1, SW1.1, SW1.2
unnamed: R59.1, SW2.1, SW2.2
unnamed: R61.2, R62.2, R63.1, R64.2
unnamed: R76.2, R77.1, U17.7
unnamed: R85.2, R86.1, U18.7
unnamed: R94.2, R95.1, U19.7
unnamed: R103.2, R104.1, U20.7
unnamed: R112.2, R113.1, U21.7
unnamed: R121.2, R122.1, U22.7
unnamed: R130.2, R131.1, U23.7
unnamed: R139.2, R140.1, U24.7
unnamed: R67.2, R144.2, U15.7
unnamed: R148.2, R149.1, U25.7
unnamed: R31.2, R162.2, U12.7
unnamed: R33.2, R237.2, U13.7
unnamed: R246.2, R247.1, U44.7
unnamed: R35.2, R258.2, U14.7
unnamed: R6.1, U1.48 (Ain8+)
unnamed: R110.1, U1.47 (Ain8-)
unnamed: C12.1, U1.22 (REFOUT1)
unnamed: C13.1, U1.9 (REFOUT2)
unnamed: C14.1, U1.6 (REFOUT3)
unnamed: C15.1, U1.45 (REFOUT4)
unnamed: R28.1, R29.1, U1.23 (~SDR/DDR)
unnamed: R3.2, U3.22 (HO1)
unnamed: R5.2, U3.9 (HO2)
unnamed: C24.1, U3.32 (RES)
unnamed: R4.2, U3.37 (RT)
unnamed: C125.1, U3.30 (SS1)
unnamed: C23.1, U3.1 (SS2)
unnamed: R109.2, U4.13 (CONFIG)
unnamed: C166.2, R127.2, U4.15 (EXTCOMP)
unnamed: R72.2, R118.2, U4.9 (En/UVLO)
unnamed: L2.2, R68.1, U4.11 (ISNS+)
unnamed: R73.2, U4.7 (PG/SYNCOUT)
unnamed: R74.2, U4.14 (RT)
unnamed: R117.1, U4.19 (VCC)
unnamed: C74.1, R71.2, U4.18 (VDDA)
unnamed: R42.1, R43.2, R44.1, U7.3 (+)
unnamed: R36.2, R40.2, U7.1, U7.2 (-)
unnamed: C46.1, R39.2, R41.1, U7.5 (+)
unnamed: R38.2, R40.1, U7.6 (-)
unnamed: R45.2, R46.1, U8.4 (FB)
unnamed: L3.2, U8.2 (SW)
unnamed: C69.1, U11.22 (REFOUT1)
unnamed: C70.1, U11.9 (REFOUT2)
unnamed: C71.1, U11.6 (REFOUT3)
unnamed: C72.1, U11.45 (REFOUT4)
unnamed: R1.1, R27.1, U11.23 (~SDR/DDR)
unnamed: C10.1, R13.2, R156.1, R157.1, U12.3 (+)
unnamed: C61.1, R18.2, R158.1, R159.1, U12.2 (-)
unnamed: R160.2, U12.5 (+)
unnamed: R161.2, R162.1, U12.6 (-)
unnamed: C63.1, R14.2, R199.1, R222.1, U13.3 (+)
unnamed: C65.1, R20.2, R223.1, R224.1, U13.2 (-)
unnamed: R235.2, U13.5 (+)
unnamed: R236.2, R237.1, U13.6 (-)
unnamed: C127.1, R15.2, R252.1, R253.1, U14.3 (+)
unnamed: C163.1, R22.2, R254.1, R255.1, U14.2 (-)
unnamed: R256.2, U14.5 (+)
unnamed: R257.2, R258.1, U14.6 (-)
unnamed: C6.1, R16.2, R119.1, R126.1, U15.3 (+)
unnamed: C8.1, R24.2, R135.1, R136.1, U15.2 (-)
unnamed: R145.2, U15.5 (+)
unnamed: R137.2, R144.1, U15.6 (-)
unnamed: R81.1, R82.2, R83.1, U17.3 (+)
unnamed: R75.2, R79.2, U17.1, U17.2 (-)
unnamed: C81.1, R78.2, R80.1, U17.5 (+)
unnamed: R77.2, R79.1, U17.6 (-)
unnamed: R90.1, R91.2, R92.1, U18.3 (+)
unnamed: R84.2, R88.2, U18.1, U18.2 (-)
unnamed: C86.1, R87.2, R89.1, U18.5 (+)
unnamed: R86.2, R88.1, U18.6 (-)
unnamed: R99.1, R100.2, R101.1, U19.3 (+)
unnamed: R93.2, R97.2, U19.1, U19.2 (-)
unnamed: C91.1, R96.2, R98.1, U19.5 (+)
unnamed: R95.2, R97.1, U19.6 (-)
unnamed: R102.2, R106.2, U20.1, U20.2 (-)
unnamed: C96.1, R105.2, R107.1, U20.5 (+)
unnamed: R104.2, R106.1, U20.6 (-)
unnamed: R111.2, R115.2, U21.1, U21.2 (-)
unnamed: C101.1, R114.2, R116.1, U21.5 (+)
unnamed: R113.2, R115.1, U21.6 (-)
unnamed: R120.2, R124.2, U22.1, U22.2 (-)
unnamed: C106.1, R123.2, R125.1, U22.5 (+)
unnamed: R122.2, R124.1, U22.6 (-)
unnamed: R129.2, R133.2, U23.1, U23.2 (-)
unnamed: C111.1, R132.2, R134.1, U23.5 (+)
unnamed: R131.2, R133.1, U23.6 (-)
unnamed: R138.2, R142.2, U24.1, U24.2 (-)
unnamed: C116.1, R141.2, R143.1, U24.5 (+)
unnamed: R140.2, R142.1, U24.6 (-)
unnamed: R147.2, R151.2, U25.1, U25.2 (-)
unnamed: C121.1, R150.2, R152.1, U25.5 (+)
unnamed: R149.2, R151.1, U25.6 (-)
unnamed: R220.2, R221.2, U36.5 (DIR)
unnamed: R240.2, R241.2, U42.5 (DIR)
unnamed: R245.2, R249.2, U44.1, U44.2 (-)
unnamed: C161.1, R248.2, R250.1, U44.5 (+)
unnamed: R247.2, R249.1, U44.6 (-)
REFOUT_B6: C11.1, R107.2, R116.2, R125.2, R134.2, R143.2, R152.2, R250.2, U1.8 (REF)
REFOUT_M: C6.2, C10.2, C63.2, C68.1, C127.2, R41.2, R80.2, R89.2, R98.2, R119.2, R126.2, R145.1, R156.2, R157.2, R160.1, R199.2, R222.2, R235.1, R252.2, R253.2, R256.1, U11.8 (REF)

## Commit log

2025-10-15 adding library as a submodule
2025-10-15 added first thing to lib
2025-10-27 added lib
2025-10-27 created FPGA Board project + added lib
2025-10-27 turned off backups
2025-10-28 starting schematic + added kicad lib
2025-10-29 moved Project, lib changes
2025-11-01 some changes + lib
2025-11-09 adding DCCD
2025-11-10 some work on the schematics
2025-11-10 some stuff
2025-11-11 schematic almost ready
2025-11-12 schematic almost ready pt2
2025-11-16 Besprechung mit Leo
2025-11-17 some schematic changes + Misc
2025-11-17 lot of work
2025-11-17 lots of work
2025-11-18 work
2025-11-18 18.11 Bib Session
2025-11-19 19.11
2025-11-23 22.11
2025-11-23 exported stuff
2025-12-01 added Wannenstecker 24pin + BOM
2025-12-10 schematic fixes after Leo Meeting
2025-12-10 started component placement
2025-12-12 placement of Power DCDC and Buffers ready
2025-12-13 arranged level shifters in schematic + solid progress in layout
2025-12-13 layout of islands is ready
2025-12-16 Component placement ready. Waiting to meet with Leo
2025-12-16 Placement optimised
2025-12-17 component placement with new concept is ready
2025-12-17 started power DCDC layout
2025-12-20 DCDC Converter layout almost ready
2025-12-21 small changes in the PCB
2025-12-23 added user manual
2025-12-24 started routing of the right side
2025-12-24 right side almost finished
2025-12-25 some changes in the PCB
2025-12-26 some minimal changes on the PCB on the right side
2025-12-26 added bus into schematic
2025-12-27 big schematic cleanup. Added wire to bus
2025-12-28 PCB left side almost finished + some optimization in schematics
2025-12-28 added 5V supply for Zynq
2025-12-29 layed out power supply for Zynq
2025-12-30 optimised pinout in schematic + added level shifter for CLKOUT + got forward with layout
2025-12-31 fixed wire bus in schematic + routing almost ready, only routing of power is left
2025-12-31 layout 99% ready
2026-01-01 layout ready to be reviewed by Leo
2026-01-24 Nach meeting mit Leo
2026-01-25 final layout almost ready (onlypower is left)
2026-01-25 PCB ready to be ordered
2026-02-26 added Leo edit
2026-02-26 improvements.txt + lib
2026-03-02 Adding drawings to PCB + Improvements.txt
2026-03-04 some
2026-03-04 Ibom + improvements
2026-03-05 imrpovements
2026-03-22 Zynq Flash löschen
2026-03-22 update improvements
2026-04-03 creating pinout docs for the Zynq board + BA Struktur
